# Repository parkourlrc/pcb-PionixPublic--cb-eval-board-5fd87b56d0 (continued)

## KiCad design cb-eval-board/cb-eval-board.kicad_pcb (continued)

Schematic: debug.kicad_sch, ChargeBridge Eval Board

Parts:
C39: 100n; C_0603_1608Metric; MPN C0603C104K5RACAUTO; Digikey 399-6856-1-ND
J2: Conn_01x06; PinHeader_1x06_P2.54mm_Vertical; MPN TS-106-T-A; Digikey SAM1112-06-ND
R69, R79, R80, R81, R82: 330; R_0603_1608Metric; MPN RMCF0603FT330R; Digikey RMCF0603FT330RCT-ND
SW3, SW4: SW_Push; SW_TS02-66-70-BK-160-LCR-D; MPN TS02-66-70-BK-160-LCR-D; Digikey 2223-TS02-66-70-BK-160-LCR-D-ND
U1: 10128796-001RLF; AMPHENOL_10128796-001RLF_ChargeBridge_Wurth_standoff; MPN 10128796-001RLF
U8: STLINK-V3MODS; MODULE_STLINK-V3MODS; PARTREV 1; Digikey 497-STLINK-V3MODS-ND; not fitted

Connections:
+3.3V: C39.1, R69.2, U8.30 (T_VCC); also elsewhere on the board
/30V > 3.3V Power Supply/RESET#: SW3.1, U1.42 (RESET), U8.31 (T_NRST); also elsewhere on the board
/Debugging/DBG_UART_RX: J2.4, R80.1, U1.65 (UART2_RX)
/Debugging/DBG_UART_TX: J2.5, R79.1, U1.63 (UART2_TX)
/Debugging/SWCLK: R82.1, U1.1 (RESERVED/SWCLK)
/Debugging/SWDIO: R81.1, U1.5 (RESERVED/SWDIO)
GND: C39.2, J2.1, SW3.2, U8.5 (GNDDETECT), U8.8 (GND_2), U8.24 (GND), U8.26 (GND2), U8.27 (GND3), U8.29 (GND4); also elsewhere on the board
unnamed: R69.1, SW4.1
unnamed: SW4.2, U1.30 (SECURE_MODULE)
unnamed: R82.2, U8.13 (T_JCLK/T_SWCLK)
unnamed: R81.2, U8.4 (T_JTMS/T_SWDIO)
unnamed: R80.2, U8.15 (T_VCP_RX)
unnamed: R79.2, U8.12 (T_VCP_TX)

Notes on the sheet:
Allow certificates/keys to be installed while pressed. See datasheet for usage. On production boards pull to GND permanently.
Debugger is only needed for Pionix internal development
ChargeBridge Manual reset
ChargeBridge Debug UART Fits FTDI TTL-234X-3V3 cable

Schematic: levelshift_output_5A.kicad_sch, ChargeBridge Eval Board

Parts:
D4: LED YELLOW; LED_0603_1608Metric; MPN 150060AS75000; Digikey 732-150060AS75000CT-ND
R23, R36: 470; R_0603_1608Metric; MPN RMCF0603FT470R; Digikey RMCF0603FT470RCT-ND
R104: 1k; R_0603_1608Metric; MPN RMCF0603FG1K00; Digikey RMCF0603FG1K00CT-ND
R105: 100k; R_0603_1608Metric; MPN RMCF0603FT100K; Digikey RMCF0603FT100KCT-ND
U18: TPS27S100ARRKR; WQFN16_RRK_TEX; MPN TPS27S100ARRKR; Digikey 296-TPS27S100ARRKRCT-ND

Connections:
+24V: U18.9 (IN), U18.10 (IN), U18.11 (IN), U18.12 (IN); also elsewhere on the board
/Relays/LevelShiftOutputOD5/OUT: U18.5 (OUT), U18.6 (OUT), U18.7 (OUT), U18.8 (OUT); also elsewhere on the board
/Relays/RELAY3: R23.1, R104.1; also elsewhere on the board
GND: D4.1 (K), R36.2, R105.1, U18.2 (GND), U18.14 (DIAG_EN), U18.17 (GND); also elsewhere on the board
unnamed: D4.2 (A), R23.2
unnamed: R104.2, R105.2, U18.3 (EN)
unnamed: R36.1, U18.15 (ILIM)

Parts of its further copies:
D5, D6: LED YELLOW; LED_0603_1608Metric; MPN 150060AS75000; Digikey 732-150060AS75000CT-ND
R24, R27, R75, R77: 470; R_0603_1608Metric; MPN RMCF0603FT470R; Digikey RMCF0603FT470RCT-ND
R116, R118: 1k; R_0603_1608Metric; MPN RMCF0603FG1K00; Digikey RMCF0603FG1K00CT-ND
R117, R119: 100k; R_0603_1608Metric; MPN RMCF0603FT100K; Digikey RMCF0603FT100KCT-ND
U19, U20: TPS27S100ARRKR; WQFN16_RRK_TEX; MPN TPS27S100ARRKR; Digikey 296-TPS27S100ARRKRCT-ND

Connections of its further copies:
+24V: U19.9 (IN), U19.10 (IN), U19.11 (IN), U19.12 (IN), U20.9 (IN), U20.10 (IN), U20.11 (IN), U20.12 (IN); also elsewhere on the board
/Relays/LevelShiftOutputOD6/OUT: U19.5 (OUT), U19.6 (OUT), U19.7 (OUT), U19.8 (OUT); also elsewhere on the board
/Relays/LevelShiftOutputOD7/OUT: U20.5 (OUT), U20.6 (OUT), U20.7 (OUT), U20.8 (OUT); also elsewhere on the board
/Relays/RELAY1: R27.1, R118.1; also elsewhere on the board
/Relays/RELAY2: R24.1, R116.1; also elsewhere on the board
GND: D5.1 (K), D6.1 (K), R75.2, R77.2, R117.1, R119.1, U19.2 (GND), U19.14 (DIAG_EN), U19.17 (GND), U20.2 (GND), U20.14 (DIAG_EN), U20.17 (GND); also elsewhere on the board
unnamed: D5.2 (A), R24.2
unnamed: D6.2 (A), R27.2
unnamed: R116.2, R117.2, U19.3 (EN)
unnamed: R75.1, U19.15 (ILIM)
unnamed: R118.2, R119.2, U20.3 (EN)
unnamed: R77.1, U20.15 (ILIM)

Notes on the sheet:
5A current limit

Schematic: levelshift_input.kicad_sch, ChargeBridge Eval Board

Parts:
D11: LED YELLOW; LED_0603_1608Metric; MPN 150060AS75000; Digikey 732-150060AS75000CT-ND
D20: MM3Z5V1ST1G; D_SOD-323; MPN MM3Z5V1ST1G; Digikey MM3Z5V1ST1GOSCT-ND
R1, R28: 470; R_0603_1608Metric; MPN RMCF0603FT470R; Digikey RMCF0603FT470RCT-ND
R40: 20k; R_0603_1608Metric; MPN RMCF0603FT20K0; Digikey RMCF0603FT20K0CT-ND
R73: 1M; R_0603_1608Metric; MPN RMCF0603FT1M00; Digikey RMCF0603FT1M00CT-ND
U25: 74LVC1G17; SOT-353_SC-70-5; MPN SN74LVC1G17DCKR; Digikey 296-11934-1-ND

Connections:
+3.3V: U25.5 (VCC); also elsewhere on the board
/Buttons, RGB LED/LevelShiftInput1/OUT_3V3: R1.2; also elsewhere on the board
/Buttons, RGB LED/STOP_CHARGING: R40.2; also elsewhere on the board
GND: D11.1 (K), D20.2 (A), R73.2, U25.3 (GND); also elsewhere on the board
unnamed: D11.2 (A), R28.2
unnamed: D20.1 (K), R40.1, R73.1, U25.2
unnamed: R1.1, R28.1, U25.4

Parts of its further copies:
D12, D17, D18, D19, D21, D23, D25, D27, D29: LED YELLOW; LED_0603_1608Metric; MPN 150060AS75000; Digikey 732-150060AS75000CT-ND
D22, D24, D26, D28, D30, D32, D34, D36, D38: MM3Z5V1ST1G; D_SOD-323; MPN MM3Z5V1ST1G; Digikey MM3Z5V1ST1GOSCT-ND
R2, R3, R7, R19, R20, R21, R22, R37, R38, R39, R41, R42, R44, R45, R47, R48, R59, R61: 470; R_0603_1608Metric; MPN RMCF0603FT470R; Digikey RMCF0603FT470RCT-ND
R43, R46, R49, R52, R55, R68, R71, R74, R99: 20k; R_0603_1608Metric; MPN RMCF0603FT20K0; Digikey RMCF0603FT20K0CT-ND
R76, R78, R94, R95, R96, R97, R98, R102, R103: 1M; R_0603_1608Metric; MPN RMCF0603FT1M00; Digikey RMCF0603FT1M00CT-ND
U26, U27, U28, U29, U30, U31, U32, U33, U34: 74LVC1G17; SOT-353_SC-70-5; MPN SN74LVC1G17DCKR; Digikey 296-11934-1-ND

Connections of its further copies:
+3.3V: U26.5 (VCC), U27.5 (VCC), U28.5 (VCC), U29.5 (VCC), U30.5 (VCC), U31.5 (VCC), U32.5 (VCC), U33.5 (VCC), U34.5 (VCC); also elsewhere on the board
/Buttons, RGB LED/EMERGENCY_SHDN_IN: R43.2; also elsewhere on the board
/Buttons, RGB LED/LevelShiftInput2/OUT_3V3: R2.2; also elsewhere on the board
/GPIO9: R61.2; also elsewhere on the board
/GPIOs/LevelShiftInput3/IN: R46.2; also elsewhere on the board
/GPIOs/LevelShiftInput3/OUT_3V3: R3.2; also elsewhere on the board
/GPIOs/LevelShiftInput4/IN: R49.2; also elsewhere on the board
/GPIOs/LevelShiftInput4/OUT_3V3: R7.2; also elsewhere on the board
/GPIOs/LevelShiftInput5/IN: R52.2; also elsewhere on the board
/GPIOs/LevelShiftInput5/OUT_3V3: R19.2; also elsewhere on the board
/GPIOs/LevelShiftInput6/IN: R55.2; also elsewhere on the board
/GPIOs/LevelShiftInput6/OUT_3V3: R20.2; also elsewhere on the board
/GPIOs/LevelShiftInput10/IN: R99.2; also elsewhere on the board
/Relays/LevelShiftInput7/IN: R68.2; also elsewhere on the board
/Relays/LevelShiftInput8/IN: R71.2; also elsewhere on the board
/Relays/LevelShiftInput9/IN: R74.2; also elsewhere on the board
/Relays/RELAY1_FB: R21.2; also elsewhere on the board
/Relays/RELAY2_FB: R22.2; also elsewhere on the board
/Relays/RELAY3_FB: R59.2; also elsewhere on the board
GND: D12.1 (K), D17.1 (K), D18.1 (K), D19.1 (K), D21.1 (K), D22.2 (A), D23.1 (K), D24.2 (A), D25.1 (K), D26.2 (A), D27.1 (K), D28.2 (A), D29.1 (K), D30.2 (A), D32.2 (A), D34.2 (A), D36.2 (A), D38.2 (A), R76.2, R78.2, R94.2, R95.2, R96.2, R97.2, R98.2, R102.2, R103.2, U26.3 (GND), U27.3 (GND), U28.3 (GND), U29.3 (GND), U30.3 (GND), U31.3 (GND), U32.3 (GND), U33.3 (GND), U34.3 (GND); also elsewhere on the board
unnamed: D12.2 (A), R37.2
unnamed: D17.2 (A), R38.2
unnamed: D18.2 (A), R39.2
unnamed: D19.2 (A), R41.2
unnamed: D21.2 (A), R42.2
unnamed: D22.1 (K), R43.1, R76.1, U26.2
unnamed: D23.2 (A), R44.2
unnamed: D24.1 (K), R46.1, R78.1, U27.2
unnamed: D25.2 (A), R45.2
unnamed: D26.1 (K), R49.1, R94.1, U28.2
unnamed: D27.2 (A), R47.2
unnamed: D28.1 (K), R52.1, R95.1, U29.2
unnamed: D29.2 (A), R48.2
unnamed: D30.1 (K), R55.1, R96.1, U30.2
unnamed: D32.1 (K), R68.1, R97.1, U31.2
unnamed: D34.1 (K), R71.1, R98.1, U32.2
unnamed: D36.1 (K), R74.1, R102.1, U33.2
unnamed: D38.1 (K), R99.1, R103.1, U34.2
unnamed: R2.1, R37.1, U26.4
unnamed: R3.1, R38.1, U27.4
unnamed: R19.1, R41.1, U29.4
unnamed: R20.1, R42.1, U30.4
unnamed: R21.1, R44.1, U31.4
unnamed: R22.1, R45.1, U32.4
unnamed: R7.1, R39.1, U28.4
unnamed: R47.1, R59.1, U33.4
unnamed: R48.1, R61.1, U34.4

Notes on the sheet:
30V tolerant input

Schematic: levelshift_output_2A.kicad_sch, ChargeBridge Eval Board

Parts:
D31: LED YELLOW; LED_0603_1608Metric; MPN 150060AS75000; Digikey 732-150060AS75000CT-ND
R50: 470; R_0603_1608Metric; MPN RMCF0603FT470R; Digikey RMCF0603FT470RCT-ND
R56, R106: 1k; R_0603_1608Metric; MPN RMCF0603FG1K00; Digikey RMCF0603FG1K00CT-ND
R107: 100k; R_0603_1608Metric; MPN RMCF0603FT100K; Digikey RMCF0603FT100KCT-ND
U13: TPS27S100ARRKR; WQFN16_RRK_TEX; MPN TPS27S100ARRKR; Digikey 296-TPS27S100ARRKRCT-ND

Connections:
+24V: U13.9 (IN), U13.10 (IN), U13.11 (IN), U13.12 (IN); also elsewhere on the board
/GPIOs/LevelShiftOutputOD/IN: R50.1, R106.1; also elsewhere on the board
/GPIOs/LevelShiftOutputOD/OUT: U13.5 (OUT), U13.6 (OUT), U13.7 (OUT), U13.8 (OUT); also elsewhere on the board
GND: D31.1 (K), R56.2, R107.1, U13.2 (GND), U13.14 (DIAG_EN), U13.17 (GND); also elsewhere on the board
unnamed: D31.2 (A), R50.2
unnamed: R106.2, R107.2, U13.3 (EN)
unnamed: R56.1, U13.15 (ILIM)

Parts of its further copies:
D1, D33, D35, D37, D39: LED YELLOW; LED_0603_1608Metric; MPN 150060AS75000; Digikey 732-150060AS75000CT-ND
R31, R51, R53, R54, R57: 470; R_0603_1608Metric; MPN RMCF0603FT470R; Digikey RMCF0603FT470RCT-ND
R58, R60, R62, R64, R65, R67, R108, R110, R112, R114: 1k; R_0603_1608Metric; MPN RMCF0603FG1K00; Digikey RMCF0603FG1K00CT-ND
R66, R109, R111, R113, R115: 100k; R_0603_1608Metric; MPN RMCF0603FT100K; Digikey RMCF0603FT100KCT-ND
U14, U15, U16, U17, U21: TPS27S100ARRKR; WQFN16_RRK_TEX; MPN TPS27S100ARRKR; Digikey 296-TPS27S100ARRKRCT-ND

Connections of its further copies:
+24V: U14.9 (IN), U14.10 (IN), U14.11 (IN), U14.12 (IN), U15.9 (IN), U15.10 (IN), U15.11 (IN), U15.12 (IN), U16.9 (IN), U16.10 (IN), U16.11 (IN), U16.12 (IN), U17.9 (IN), U17.10 (IN), U17.11 (IN), U17.12 (IN), U21.9 (IN), U21.10 (IN), U21.11 (IN), U21.12 (IN); also elsewhere on the board
/Buttons, RGB LED/EMERGENCY_SHDN_OUT: U21.5 (OUT), U21.6 (OUT), U21.7 (OUT), U21.8 (OUT); also elsewhere on the board
/Buttons, RGB LED/LevelShiftOutputOD3/IN: R31.1, R65.1; also elsewhere on the board
/GPIOs/LevelShiftOutputOD1/IN: R51.1, R108.1; also elsewhere on the board
/GPIOs/LevelShiftOutputOD1/OUT: U14.5 (OUT), U14.6 (OUT), U14.7 (OUT), U14.8 (OUT); also elsewhere on the board
/GPIOs/LevelShiftOutputOD2/IN: R53.1, R110.1; also elsewhere on the board
/GPIOs/LevelShiftOutputOD2/OUT: U15.5 (OUT), U15.6 (OUT), U15.7 (OUT), U15.8 (OUT); also elsewhere on the board
/GPIOs/LevelShiftOutputOD3/IN: R54.1, R112.1; also elsewhere on the board
/GPIOs/LevelShiftOutputOD3/OUT: U16.5 (OUT), U16.6 (OUT), U16.7 (OUT), U16.8 (OUT); also elsewhere on the board
/GPIOs/LevelShiftOutputOD4/IN: R57.1, R114.1; also elsewhere on the board
/GPIOs/LevelShiftOutputOD4/OUT: U17.5 (OUT), U17.6 (OUT), U17.7 (OUT), U17.8 (OUT); also elsewhere on the board
GND: D1.1 (K), D33.1 (K), D35.1 (K), D37.1 (K), D39.1 (K), R58.2, R60.2, R62.2, R64.2, R66.1, R67.2, R109.1, R111.1, R113.1, R115.1, U14.2 (GND), U14.14 (DIAG_EN), U14.17 (GND), U15.2 (GND), U15.14 (DIAG_EN), U15.17 (GND), U16.2 (GND), U16.14 (DIAG_EN), U16.17 (GND), U17.2 (GND), U17.14 (DIAG_EN), U17.17 (GND), U21.2 (GND), U21.14 (DIAG_EN), U21.17 (GND); also elsewhere on the board
unnamed: D1.2 (A), R31.2
unnamed: D33.2 (A), R51.2
unnamed: D35.2 (A), R53.2
unnamed: D37.2 (A), R54.2
unnamed: D39.2 (A), R57.2
unnamed: R108.2, R109.2, U14.3 (EN)
unnamed: R58.1, U14.15 (ILIM)
unnamed: R110.2, R111.2, U15.3 (EN)
unnamed: R60.1, U15.15 (ILIM)
unnamed: R112.2, R113.2, U16.3 (EN)
unnamed: R62.1, U16.15 (ILIM)
unnamed: R114.2, R115.2, U17.3 (EN)
unnamed: R64.1, U17.15 (ILIM)
unnamed: R65.2, R66.2, U21.3 (EN)
unnamed: R67.1, U21.15 (ILIM)

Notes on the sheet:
2A current limit

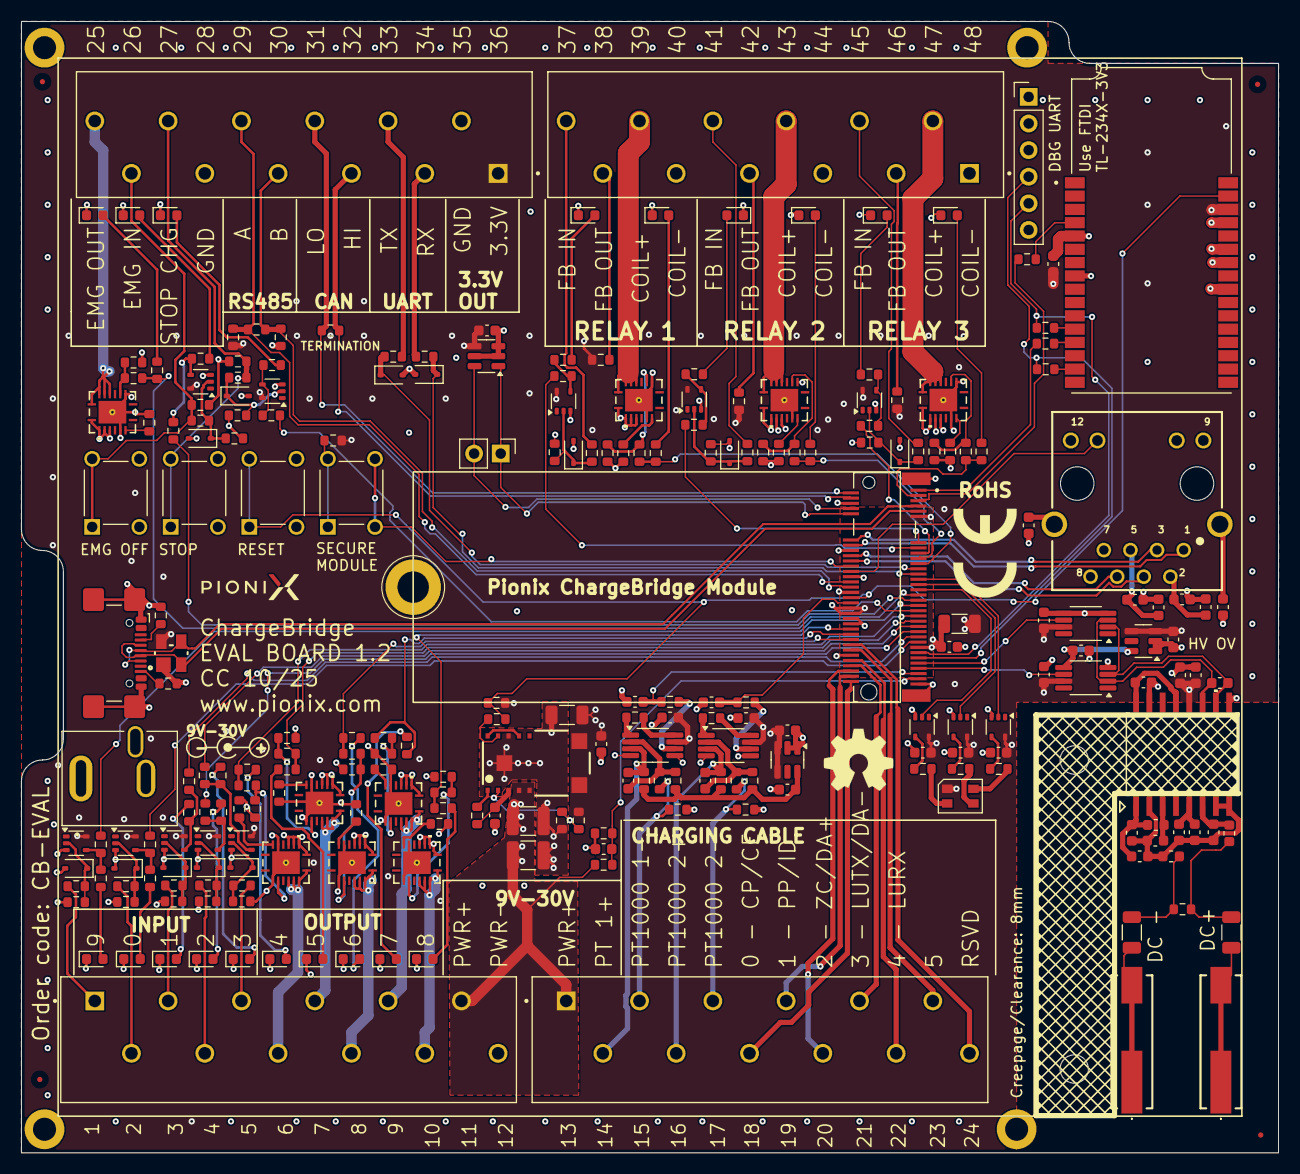
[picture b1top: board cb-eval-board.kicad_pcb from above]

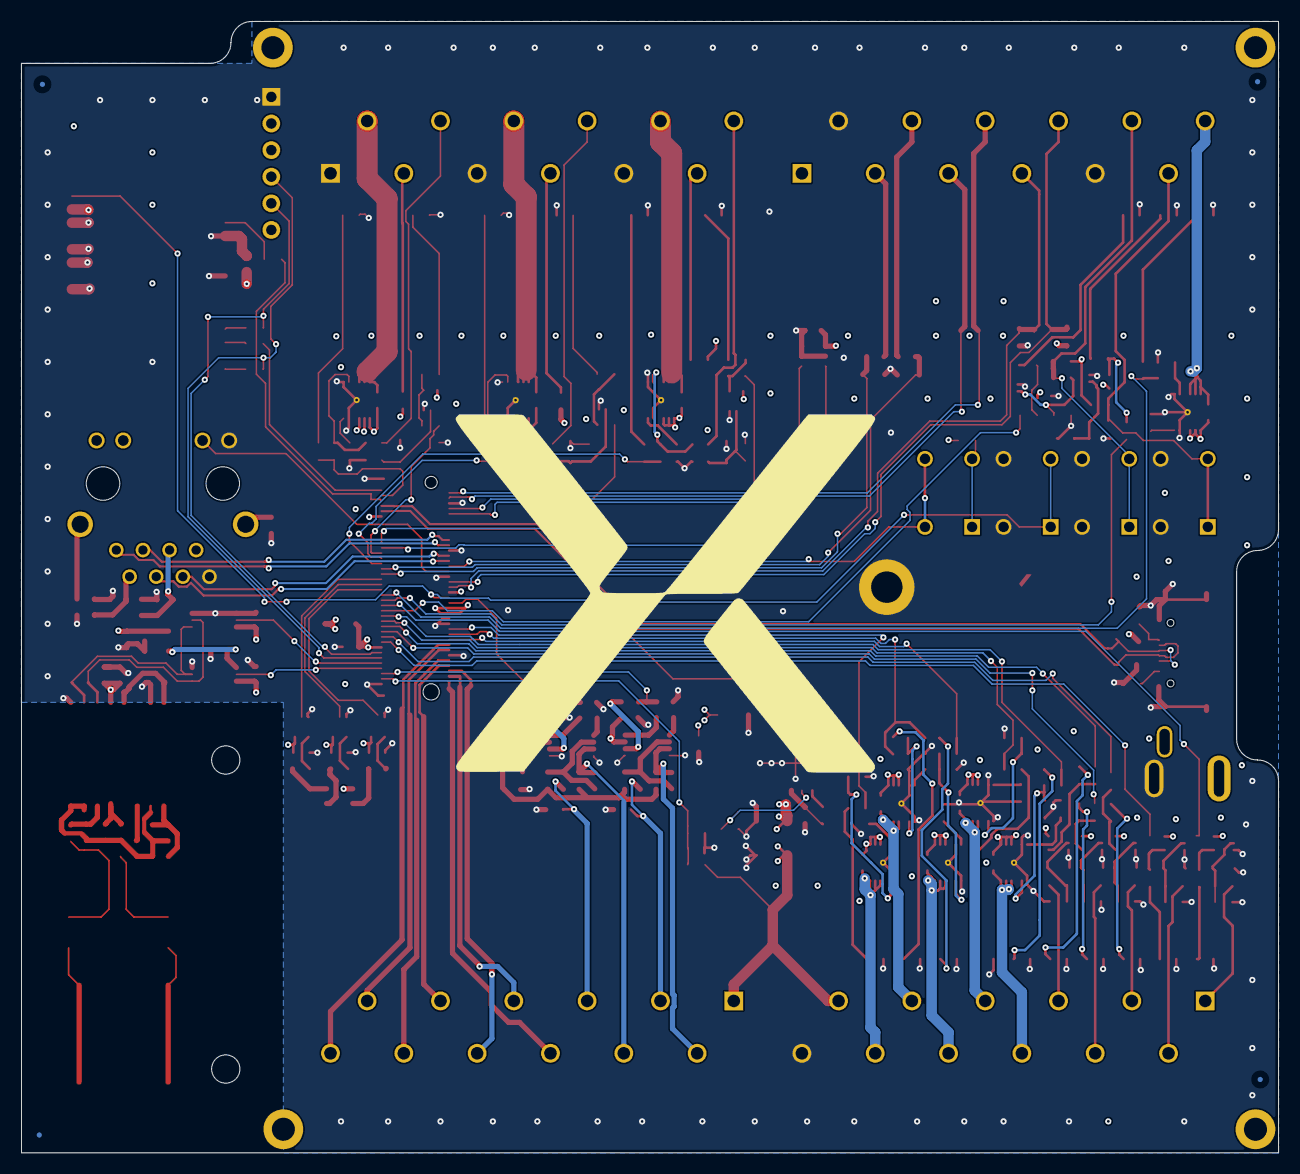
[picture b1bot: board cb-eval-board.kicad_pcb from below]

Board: 4 copper layers, 120.0 x 108.0 mm, 264 parts (5 on the bottom side), 188 nets.

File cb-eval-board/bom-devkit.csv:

"Reference","Value","Footprint","Qty","DNP","Manufacturer","MPN","Mouser","Digikey"
"C1,C2,C3,C9,C11,C12,C13,C14,C15,C21,C25,C26,C30,C31,C34,C36,C37,C39,C42,C45","100n","Capacitor_SMD:C_0603_1608Metric","20","","Kemet","C0603C104K5RACAUTO","","399-6856-1-ND"
"C4,C7,C22,C23,C32,C43,C44","1u","Capacitor_SMD:C_0603_1608Metric","7","","Kemet","C0603C105K3PACTU","","399-C0603C105K3PACTUCT-ND"
"C5,C6","4.7u 50V","Capacitor_SMD:C_1210_3225Metric","2","","TDK Corporation","C3225X7R1H475K250AB","","445-7726-1-ND"
"C8","10u","Capacitor_SMD:C_0603_1608Metric","1","","Murata Electronics","GRM188R6YA106MA73J","","490-GRM188R6YA106MA73JCT-ND"
"C10","100u 6.3V","Capacitor_SMD:C_1206_3216Metric","1","","Taiyo Yuden","JMK316ABJ107ML-T","","587-3395-1-ND"
"C20,C24,C27,C33,C35,C40,C41","1n","Capacitor_SMD:C_0603_1608Metric","7","","Kemet","C0603C102K5RACTU","","399-C0603C102K5RACTUCT-ND"
"C28,C29","100p","Capacitor_SMD:C_0603_1608Metric","2","","Walsin Technology Corporation","0603N101J500CT","","1292-1644-1-ND"
"D1,D4,D5,D6,D11,D12,D17,D18,D19,D21,D23,D25,D27,D29,D31,D33,D35,D37,D39","LED YELLOW","LED_SMD:LED_0603_1608Metric","19","","Würth Elektronik","150060AS75000","","732-150060AS75000CT-ND"
"D8","CLV1L-FKB","cb-eval-lib:LED_Cree-PLCC4_3.2x2.8mm_CCW","1","","Cree LED","CLV1L-FKB-CJQRNQEFGBB79353","","90-CLV1L-FKB-CJQRNQEFGBB79353CT-ND"
"D9,D10","MM3Z3V3ST1G","Diode_SMD:D_SOD-323","2","","onsemi","MM3Z3V3ST1G","","MM3Z3V3ST1GOSCT-ND"
"D20,D22,D24,D26,D28,D30,D32,D34,D36,D38","MM3Z5V1ST1G","Diode_SMD:D_SOD-323","10","","onsemi","MM3Z5V1ST1G","","MM3Z5V1ST1GOSCT-ND"
"D41","5Vdc","cb-eval-lib:WE-TVS_SOT143-4L","1","","Eaton - Electronics Division","STS142050UL08","","283-STS142050UL08CT-ND"
"FB1,FB2,FB3","1.8k@100MHz","Inductor_SMD:L_0603_1608Metric","3","","Wurth Elektronik","742792692","","732-4671-1-ND"
"H7","Standoff_M.2","cb-eval-lib:9774067243R","1","","Würth Elektronik","9774067243R","",""
"J1,J6","Conn_01x01","cb-eval-lib:2060451998404","2","","Wago","2060-451/998-404","","2946-2060-451/998-404CT-ND"
"J2","Conn_01x06","Connector_PinHeader_2.54mm:PinHeader_1x06_P2.54mm_Vertical","1","","Samtec Inc.","TS-106-T-A","","SAM1112-06-ND"
"J3","I3C","Connector_PinHeader_2.54mm:PinHeader_1x02_P2.54mm_Vertical","1","Nicht bestücken","NONE ","DNP","",""
"J4,J5,J7,J11","TBL002A-350-12GY-2GY","cb-eval-lib:CUI_TBL002A-350-12GY-2GY","4","","Same Sky (Formerly CUI Devices)","TBL002A-350-12GY-2GY","","102-6375-ND"
"J9","USB_C_Receptacle_USB2.0_14P","cb-eval-lib:USB_C_Receptacle_GCT_USB4110","1","","GCT","USB4110-GF-A","","2073-USB4110-GF-A-1-ND"
"J10","Barrel_Jack_Switch","cb-eval-lib:CUI_PJ-044AH","1","","Same Sky (Formerly CUI Devices)","PJ-044AH","","CP-044AH-ND"
"R1,R2,R3,R7,R13,R15,R17,R18,R19,R20,R21,R22,R23,R24,R27,R28,R31,R36,R37,R38,R39,R41,R42,R44,R45,R47,R48,R50,R51,R53,R54,R57,R59,R61,R75,R77","470","Resistor_SMD:R_0603_1608Metric","36","","Stackpole Electronics Inc","RMCF0603FT470R","","RMCF0603FT470RCT-ND"
"R4,R5,R6,R10,R11,R69,R79,R80,R81,R82","330","Resistor_SMD:R_0603_1608Metric","10","","Stackpole Electronics Inc","RMCF0603FT330R","","RMCF0603FT330RCT-ND"
"R8,R9,R25,R66,R88,R93,R105,R107,R109,R111,R113,R115,R117,R119","100k","Resistor_SMD:R_0603_1608Metric","14","","Stackpole Electronics Inc","RMCF0603FT100K","","RMCF0603FT100KCT-ND"
"R12","68","Resistor_SMD:R_0603_1608Metric","1","","Stackpole Electronics Inc","RMCF0603FT68R0","","RMCF0603FT68R0CT-ND"
"R14,R16","120","Resistor_SMD:R_0603_1608Metric","2","","Stackpole Electronics Inc","RMCF0603FT120R","","RMCF0603FT120RCT-ND"
"R26,R33","5.6k","Resistor_SMD:R_0603_1608Metric","2","","Stackpole Electronics Inc","RMCF0603FT5K60","","RMCF0603FT5K60CT-ND"
"R29,R83","6M 0.5%","Resistor_SMD:R_1206_3216Metric","2","","Vishay Techno","CRMA1206AF6M00DKEF","","3579-CRMA1206AF6M00DKEFCT-ND"
"R30","20k 0.1%","Resistor_SMD:R_0603_1608Metric","1","","Panasonic Electronic Components","ERA-3AEB203V","","P20KDBCT-ND"
"R32","10k","Resistor_SMD:R_0603_1608Metric","1","","Stackpole Electronics Inc","RMCF0603FT10K0","","RMCF0603FT10K0CT-ND"
"R34","402k","Resistor_SMD:R_0603_1608Metric","1","","Stackpole Electronics Inc","RMCF0603FT402K","",""
"R35","137k","Resistor_SMD:R_0603_1608Metric","1","","Stackpole Electronics Inc","RMCF0603FT137k","",""
"R40,R43,R46,R49,R52,R55,R68,R71,R74,R99","20k","Resistor_SMD:R_0603_1608Metric","10","","Stackpole Electronics Inc","RMCF0603FT20K0","","RMCF0603FT20K0CT-ND"
"R56,R58,R60,R62,R64,R65,R67,R104,R106,R108,R110,R112,R114,R116,R118","1k","Resistor_SMD:R_0603_1608Metric","15","","Stackpole Electronics Inc","RMCF0603FG1K00","","RMCF0603FG1K00CT-ND"
"R63","50m","Resistor_SMD:R_1206_3216Metric","1","","Stackpole Electronics Inc","CSR1206FT50L0","","CSR1206FT50L0CT-ND"
"R70,R72,R84,R86,R89,R91","4.99k 0.1%","Resistor_SMD:R_0603_1608Metric","6","","Panasonic Electronic Components","ERA-3AEB4991V","","P4.99KDBCT-ND"
"R73,R76,R78,R94,R95,R96,R97,R98,R102,R103","1M","Resistor_SMD:R_0603_1608Metric","10","","Stackpole Electronics Inc","RMCF0603FT1M00","","RMCF0603FT1M00CT-ND"
"R85,R90","825 0.1%","Resistor_SMD:R_0603_1608Metric","2","","Panasonic Electronic Components","ERA-3AEB8250V","","P909DBCT-ND"
"R87,R92","3.44k 0.1%","Resistor_SMD:R_0603_1608Metric","2","","Panasonic Electronic Components","RN73R1JTTD3441B25","","P8.2KDBCT-ND"
"R100,R101","5.1k","Resistor_SMD:R_0603_1608Metric","2","","Stackpole Electronics Inc","RMCF0603FT5K10","","RMCF0603FT5K10CT-ND"
"R120","0","Resistor_SMD:R_0603_1608Metric","1","","Stackpole Electronics Inc","RMCF0603ZT0R00","","RMCF0603ZT0R00CT-ND"
"SW1,SW2,SW3,SW4","SW_Push","cb-eval-lib:SW_TS02-66-70-BK-160-LCR-D","4","","Same Sky (Formerly CUI Devices)","TS02-66-70-BK-160-LCR-D","","2223-TS02-66-70-BK-160-LCR-D-ND"
"T1","74990101241","cb-eval-lib:74990101241","1","","Wurth Elektronik","74990101241","","732-10834-ND"
"U1","10128796-001RLF","cb-eval-lib:AMPHENOL_10128796-001RLF_ChargeBridge_Wurth_standoff","1","","Amphenol ICC (FCI)","10128796-001RLF","",""
"U2,U3,U4,U25,U26,U27,U28,U29,U30,U31,U32,U33,U34","74LVC1G17","Package_TO_SOT_SMD:SOT-353_SC-70-5","13","","Texas Instruments","SN74LVC1G17DCKR","","296-11934-1-ND"
"U5","TMP100","Package_TO_SOT_SMD:SOT-23-6","1","","Texas Instruments","TMP100NA/3K","","296-26833-1-ND"
"U6","AMC3311DWER","cb-eval-lib:SOIC16_7P5X10P3_TEX","1","","Texas Instruments","AMC3311DWER","","296-AMC3311DWERCT-ND"
"U9,U11,U22,U23","INA333AIDGKR","cb-eval-lib:VSSOP-8_3x3mm_P0.65mm","4","","Texas Instruments","INA333AIDGKR","","296-23564-1-ND"
"U10,U24","REF35205QDBVR","Package_TO_SOT_SMD:SOT-23-6","2","","Texas Instruments","REF35205QDBVR","","296-REF35205QDBVRCT-ND"
"U13,U14,U15,U16,U17,U18,U19,U20,U21","TPS27S100ARRKR","cb-eval-lib:WQFN16_RRK_TEX","9","","Texas Instruments","TPS27S100ARRKR","","296-TPS27S100ARRKRCT-ND"
"U37","171023801","cb-eval-lib:WPME-VDLM_LGA-12EP","1","","Würth Elektronik","171023801","","732-171023801CT-ND"

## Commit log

2025-12-01 Version 1.2
